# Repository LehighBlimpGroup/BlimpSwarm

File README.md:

# BLIMP SWARM
## [Click here for Documentation!](https://lehighblimpgroup.github.io/BlimpSwarm/)

BlimpSwarm is a framework to operate robots based on the ESP32 microcontroler.
### Please find [the indexed documentation here](https://github.com/LehighBlimpGroup/BlimpSwarm/blob/main/docs/index.md).

## FAQ

### Hardware

* Why does does only one servo or one motor not work, but the rest seem operational?
You likely have a loose/broken cable connection; If the cables are not broken (and need soldering or reinserting into the connecters), try just pushing the connectors together at every intersection. This can sometimes help the mechanical connecton to reoccur. 
If this does not solve your issue with one particular motor or servo, you might have a broken speed controller or a broken servo. Try using a test servo or test motor program to test these (or a servo tester if you have one). The motor itself can also break, and you can feel it by turining them by hand and observing the consistancy of the turning. The servo can be simalarly tested, but a servo is easier to break in this way. You can usually check if the servo is correcly powered by softly attempting to move them as they are powered and seeing if they want to move. One known issue is breaking servos due to insufficent current from the voltage booster. 

* Why does everything (motors and servos) turn on, but the robot doesnt seem to move up?
You likely have inverted motors or propellers. Make sure the propellers are correctly spinning in the correct direction and are pushing air down instead of up. If they are inverted, you need to switch any two wires in the connectors. You will need a sharp object to carefully lift the plastic blockers in the connecter to remove the wires and reinsert them in opposite positions (would recommend looking at a video).
Your robot might also be too heavy. 

* Why after I tried using all your troubleshooting tips, and I still cant solve the problem; I even used some methods you didnt mention and they failed!
There is a good chance the hardware on the PCB or the ESP32 failed. You may want to try replacing these to isolate the issue if possible to see if the issue still occurs. You may also be using an old version of the code, and may want to update the entire library to the github version. Sometimes the transeiver reduces in efficency from overuse, and the harware on the PCB can fail due to current spikes during operation. 

### Firmware

* The servos keep moving to weird positions when I start up, even though I set them to point up when the robot is in 'powered rest'. ( powered rest is the base setpoint of the servos when at rest, they should be pointing straight up).
This can be caused by the pitch feedback, try turning it off when trying. If you want pitch feedback and turining it off fixed this issue: set the pitch_offset parameter to 180 degrees from its current value. 

* Why does the flight work most of the time, but the turning while moving fowards seems very strange?
You likely have your servo1 connected to motor2 and vice versa. Check your hardware connections to make sure the front servo connection is on the same pair as the front motor connection. 

* Why does the pitch feedback fail force the servos to point straight up when it pitches, and go in the opposite direction?
Try setting inverting pitch_invert on the ground station from -1 to 1 or vice versa. 

* Why does my robot spin out of control when I start it up?
Try unplugging and replugging the blimp rapidly. Sometimes the capacitor causes the startup of the BNO to fail, and it will need a restart to correctly startup. 
Your yaw is likely inverted from the correct direction; try setting your kddyaw to negative or positive from its current direction. This is usally caused by the BNO being mounted upside down, but if that is required, you may need to edit the gains to accomidate for this. You can also double check by turining off yaw_en for yaw feedback, but your robot might unintentionally move in yaw due to the difference in servo angles when you first calibrate them. 

### Ground Station

* Why doesnt serial doesnt seem to be importing even though I did '$pip install pyserial'?: 
Your text editor is likely using a different version of python than the one you installed pyserial to: check to make sure these match or install pyserial to the installation of python used by your terminal/text editor.

* Why do I keep getting messages like "could not open port" when I run the ground station code?:
There are several reasons this could occur. 
#1 Make sure that your transiever code contains the correct 'BaseTranseiver.ino' code. 
#2 Make sure that your transiever arduino is connected to your computer, and check its port matches the one in 'user_parameters.py'.
#3 Make sure that the serial monitor of the transiever arduino is closed/not occupied by another process.

* Why isn't my blimp moving even though I turned the prorgram on?
#1 Make sure the robot is turned on.
    #a Make sure that you are sending an 'on' command in the python program (most use 'B' on the controller to start).
#2 Make sure the mac address in 'user_parameters.py' matches the mac address on the blimp.
#3 Make sure the robot code is correct: one of the bicopter.ino files ex: 'MultiRobotBicopter.ino'.
#4 Make sure the battery is charged (using a battery checker or at minimum, you hear the ESCs arm when you plug the battery in).
#5 Make sure the motors are calibrated, as the calibration might result in not seeing the motors move. 
#6 If the above fail, you can follow the following debugging procedures to isolate the issue:
#a Plug in the serial cable to the robot and observe the serial monitor:
    If the serial monitor is not printing statements that have to do with the start of a robot, or sensor measurements; you likely have the wrong firmware.
    If the serial montior is working as normal, continue.
#b Check the mac address of the robot and match it to the one in 'user_parameters.py'.
    If they are different, change and test again.
#c While observing the serial monitor, turn on the ground station code. You should see commands being recieved by the blimp on the serial monitor. (this will require two USB ports and cables) (You should not have the battery plugged into the blimp for this, unless you want to see the motors turn on while observing the serial monitor.)
    If you see nothing, you likely have some transmitter/reciever issues, but I would double check the firmware on the transeiver code, and the mac and ports are matching up on 'user_parameters.py'.
    If you see commands being recieved, you likely have a working robot, but if it still doesnt work, I would check to make sure the battery is OK and that the cables are connected correctly. Mismatches in the wiring could cause no movement even when commands are being received.

### Nicla Vision

* If you are not getting feedback from your niclavison on your arduino, you may try some of the following steps:
#1 double check that the nicla has the correct code, and it is properly downloaded on board as 'main.py'.
#2 connect the Serial monitor of your ESP32 on the blimp to the computer and make sure the nicla is powered and connected to the ESP32. Check to see if the serial monitor is getting values in the sensor measurements of the nicla (values 11-20) and that they are not crazy large values that occur when the nicla has not started up yet.
#3 double check that the nicla is properly powered, or directly connect it to your computer with a cable (will require 2 USB ports and cables)
    If you are sure that your nicla is seeing things and sending values, and you do not see anything on the ESP32 side even thought they are connected, you could have a broken Nicla vison or Nicla vision PCB. Check both by replacing them one at a time to see which is actually broken. The ESP32 PCB might also be broken but it is less likely.

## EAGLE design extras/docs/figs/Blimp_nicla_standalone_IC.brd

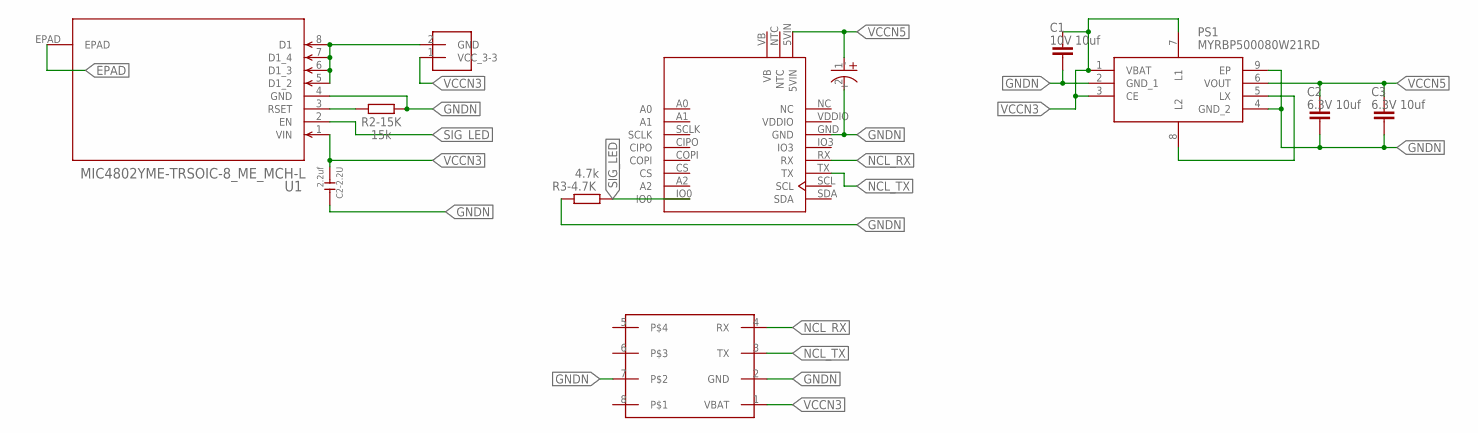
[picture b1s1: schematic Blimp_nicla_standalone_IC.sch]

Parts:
C1: 10V 10uf; CAPC1608X85
C2, C3: 6.3V 10uf; CAPC1608X85
C2-2.2U: 2.2uf; C0402
IR_LED1: UV_LIGHT
PS1: MYRBP500080W21RD
R2-15K: 15k; RESC1608X60
R3-4.7K: 4.7k; RESC1608X60
U1: MIC4802YME-TRSOIC-8_ME_MCH-L; SOIC-8_ME_MCH-L
U$6: NICLA_ESP_4PIN_CONNECTOR_MALE_ON_NICLA; ESP_NICLA_4X2PIN_CONNECTOR_MALE_ON_NICLA
U$9: CUSTOM_C; CAP
U$15: NICLAVISION; NICLA_FULL

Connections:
EPAD: U1.EPAD
GNDN: C1.2, C2.2, C2-2.2U.2, C3.2, PS1.2 (GND_1), PS1.4 (GND_2), PS1.9 (EP), R2-15K.2, R3-4.7K.2, U1.4 (GND), U$6.2 (GND), U$6.7, U$9.2 (-), U$15.GND
unnamed: IR_LED1.2 (GND), U1.5 (D1_2), U1.6 (D1_3), U1.7 (D1_4), U1.8 (D1)
unnamed: R2-15K.1, U1.3 (RSET)
unnamed: PS1.5 (LX), PS1.8 (L2)
NCL_RX: U$6.4 (RX), U$15.RX
NCL_TX: U$6.3 (TX), U$15.TX
SIG_LED: R3-4.7K.1, U1.2 (EN), U$15.IO0
VB: U$15.VB
VCCN3: C1.1, C2-2.2U.1, IR_LED1.1 (VCC_3-3), PS1.1 (VBAT), PS1.3 (CE), PS1.7 (L1), U1.1 (VIN), U$6.1 (VBAT)
VCCN5: C2.1, C3.1, PS1.6 (VOUT), U$9.1 (+), U$15.5VIN
VDDIO: U$15.VDDIO

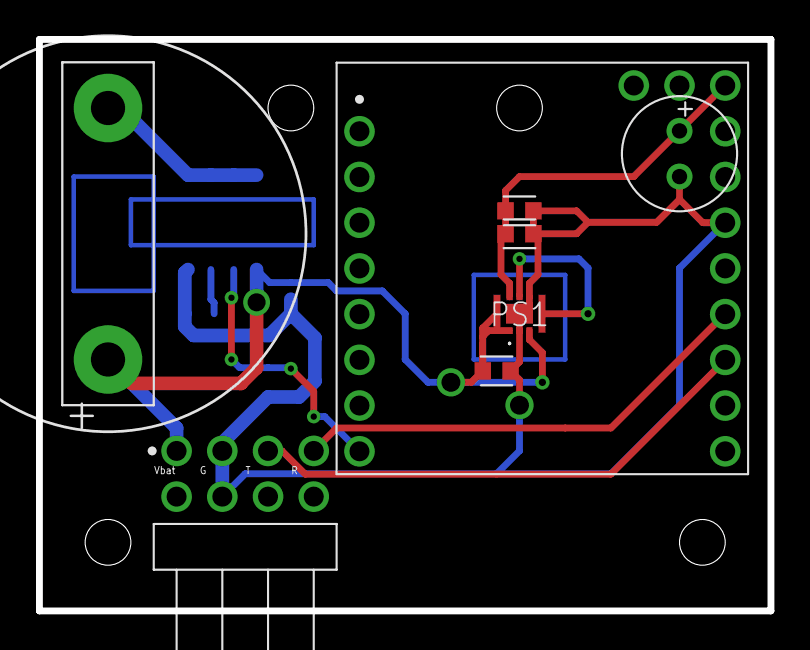
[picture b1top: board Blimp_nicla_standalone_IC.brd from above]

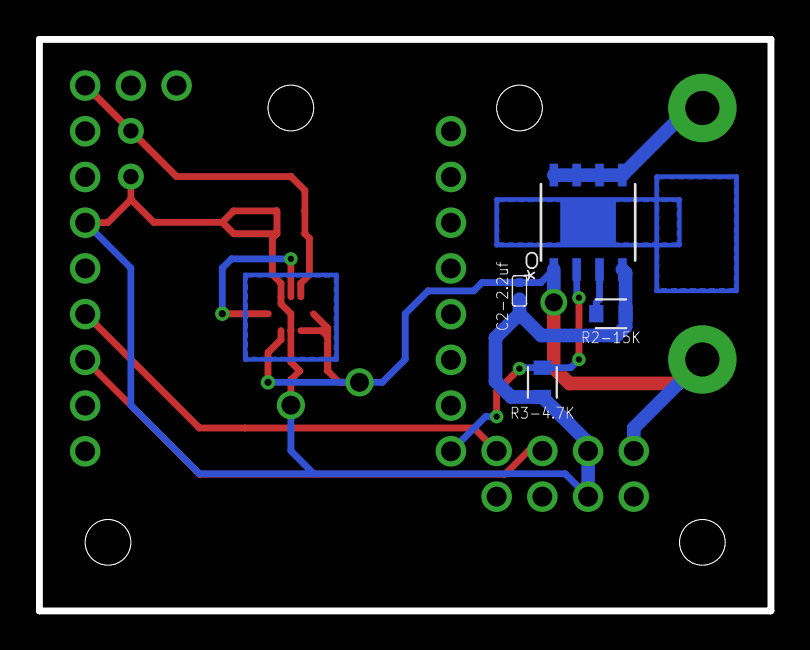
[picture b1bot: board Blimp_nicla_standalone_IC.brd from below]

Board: 2 copper layers, 40.6 x 31.8 mm, 12 parts (4 on the bottom side), 9 nets.

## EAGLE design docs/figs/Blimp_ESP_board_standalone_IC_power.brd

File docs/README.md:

# Simplest Jekyll
> A minimal Jekyll-based site on GH Pages, reduced to one page of content with a theme

<div align="center">

[_config.yml](_config.yml)
</div>

## Preview

<div align="center">
    
</div>

## About

This is a template and live demo project. It shows how little you need to setup to get a Jekyll site on GH Pages.

- [index.md](/index.md)
    - For the homepage - the only page in this case.
    - If you leave out this page, then `README.md` will be used as your homepage.
- [\_config.yml](/_config.yml)
    - Set the theme - that handles the layout and styling.
    - Enable Jekyll Sitemap plugin - enabling it in Gemfile is not enough. Note that other plugins will be enabled for you like optional frontmatter.
    - Other standard values like `baseurl`, `title` and `description` have been left out of the config. When building on GH Pages, these will be inferred for you by the GH Pages gem.
- [Gemfile](/Gemfile)
    - This is not actually used by GH Pages, but it allows you to install the Jekyll theme locally using Bundler. 
    - Use a single gem `github-pages` if you want to match all the gems on GH Pages (which can be heavy to install). 
    - Delete this file if you don't need to run your site locally.

If you want a more full-fledged example of a multi-page site with posts, gems, layouts, etc. then checkout my [jekyll-blog-demo](https://github.com/MichaelCurrin/jekyll-blog-demo) repo. That can be used as a template and demo site too.

## How to use this project

### Setup

1. Click _Use This Template_ to create a new repo in your own account. You can leave the name as `simplest-jekyll`.
2. Enable [GitHub Pages](https://pages.github.com/) in your repo's settings. Choose to serve from `master` branch and the `/` path option.
3. Check your repo's _environment_ tab to see when the deploy is done.
4. Click _View deployment_ to see the live site. e.g. https://michaelcurrin.github.io/simplest-jekyll/

Note that `/simplest-jekyll/index.html` is available immediately but it takes a few minutes until Github Pages makes `/simplest-jekyll/` available.

### Customize

- Update the `README.md` with your own details. This is not actually used in the deployed site but is visible locally and on Github.
- Themes
    - Edit the theme in [\_config.yml](/_config.yml) if you want another theme.
    - You can also use the Github Pages section of the repo Settings to preview visually. 
    - Note only themes supported by Github Pages are covered (about 10) but if you use the _remote_theme_ field in your config you can reference more themes.
    - For installing and running locally, you'll need to make sure your [Gemfile](/Gemfile) covers the theme used in the config.
- As with most Jekyll sites, the [index.md](/index.md) is used as the homepage. 
    - It has front matter at the top so any Liquid will be applied. 
    - Edit your `index.md` file with your own content as HTML or markdown. 
    - You can rename it to `index.html` if you only want plain HTML.
    - You can remove the front matter at the top to remove Liquid formatting and any theming.
- If you want to, add more pages at the root and break out any common HTMl such as header or head or navbar into `_includes` folder or `_layouts` folder (neither are covered in the scope of this project but are common for Jekyll projects).
- See the docs and tutorials on the [Jekyll](https:jekyllrb.com/) site for more info.
- Optionally run Jekyll locally:
    - Install Ruby and [Bundler](https://bundler.io).
    - Install project gems - Jekyll and the theme gem.
    - Run Jekyll dev server.
    - For fuller instructions see [docs](https://github.com/MichaelCurrin/jekyll-blog-demo/tree/master/docs) of Jekyll Blog Demo. You'll need to add a `Makefile` as well to match those commands.

## Related projects

-  - default blog generated with Jekyll CLI. Using a theme, content, style set up, gems, and a Makefile.
-  - using Jekyll 4, a theme, GitHub Actions, and GitHub Pages.
-  - minimal Jekyll site with a theme but no Gemfile.

## License

Released under [MIT](/LICENSE) by [@MichaelCurrin](https://github.com/MichaelCurrin).

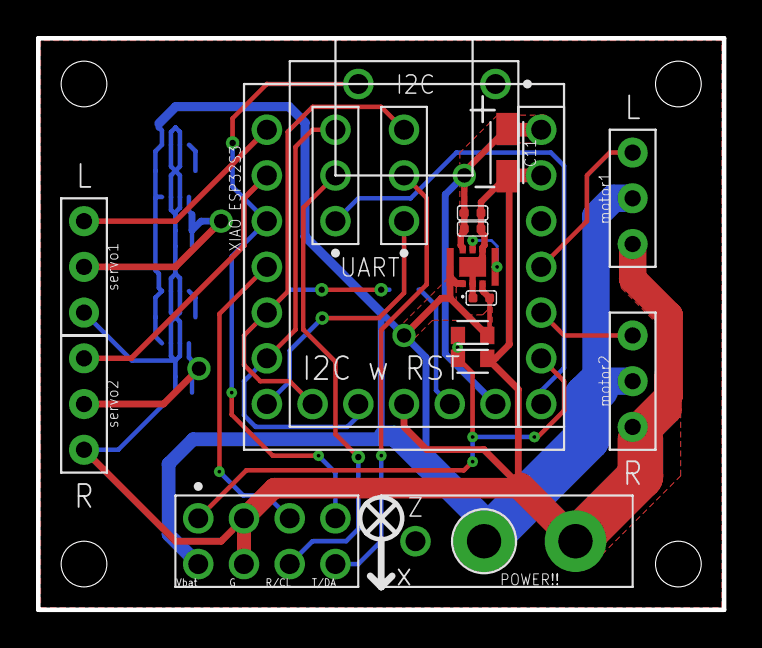
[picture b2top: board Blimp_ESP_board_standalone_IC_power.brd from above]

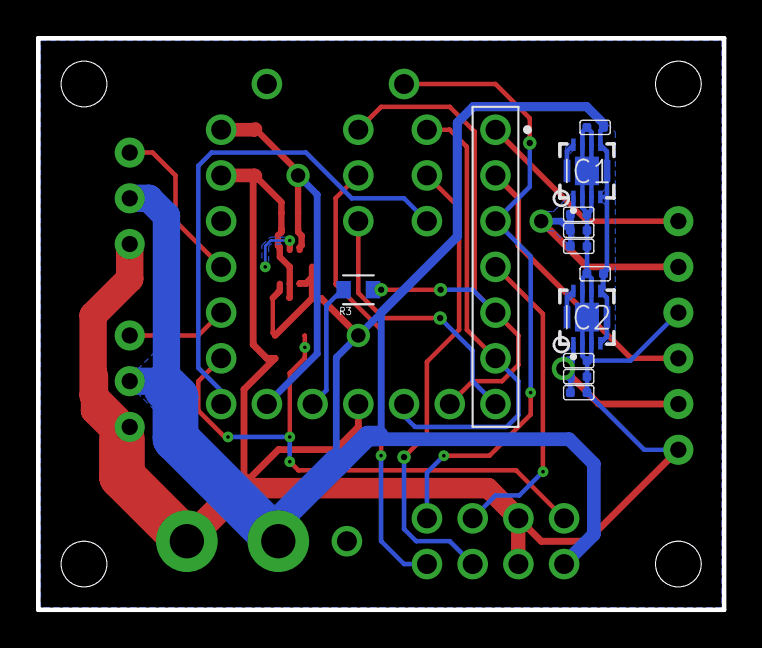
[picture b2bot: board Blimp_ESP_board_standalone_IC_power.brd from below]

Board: 2 copper layers, 38.1 x 31.8 mm, 28 parts (11 on the bottom side), 22 nets.

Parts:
ACT1, ACT2, ACT3, ACT4: ESC; ESC_CONECTOR_FOOT
C1, C2, C3, C4, C5, C6, C7, C8, C9, C10, C12: 10V 10uf; C0402
C11: CAPM3216X180
IC1, IC2: XCL104A501H2-G; DFN3030-10B
PS2: MYRBP500080W21RD
R1, R2: 470 Ohm; RESC1608X60
R3: 3.8K; RESC1608X60
U1: XIAOESP32S3
U$1: BATTERY_CONNECTOR; 3PIN_CONNECTOR_FEMALE
U$2: I2C_6PIN_WRST
U$4, U$5: 3X1SELECTOR
U$7: NICLA_ESP_4PIN_CONNECTOR_FEMALE_ON_ESP; ESP_NICLA_4X2PIN_CONNECTOR_FEMALE_ON_ESP

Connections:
3VOI2C: R3.1, U$2.9
D2: U1.3, U$2.16, U$7.4
D3: U1.4, U$7.3
D8: R1.2, R2.1, U1.9, U$7.1
ESP_RX/SCL: U$5.2, U$7.6
ESP_TX/SDA: U$4.2, U$7.5
GND: ACT1.1, ACT2.1, ACT3.1, ACT4.1, C1.2, C2.2, C3.2, C4.1, C5.2, C6.2, C7.1, C8.1, C9.1, C10.2, C11.2, C12.2, IC1.2, IC1.3, IC1.6, IC1.7, IC1.11, IC2.2, IC2.3, IC2.6, IC2.7, IC2.11, PS2.2, PS2.4, PS2.9, R2.2, U1.13, U$1.3, U$2.24, U$7.2, U$7.7
unnamed: IC1.8, IC1.9
unnamed: IC2.8, IC2.9
unnamed: PS2.5, PS2.8
RX: U1.8, U$5.1
SCL: U1.6, U$2.25, U$5.3
SDA: R3.2, U1.5, U$2.40, U$4.3
SIG1: ACT3.3, U1.1
SIG2: ACT2.3, U1.2
SIG3: ACT1.3, U1.10
SIG4: ACT4.3, U1.11
TX: U1.7, U$4.1
VBAT: ACT1.2, ACT4.2, C4.2, C7.2, C10.1, IC1.4, IC1.5, IC1.10, IC2.4, IC2.5, IC2.10, PS2.1, PS2.3, PS2.7, R1.1, U$1.2, U$7.8
VCC: C8.2, C9.2, C11.1, PS2.6, U1.14, U$2.8
VCCS1: ACT3.2, C2.1, C3.1, C12.1, IC1.1
VCCS2: ACT2.2, C1.1, C5.1, C6.1, IC2.1

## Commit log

2024-01-19 - File structure - Old files migration
2024-01-20 - Robot Factory is working - Compiled and tested on ESP
2024-01-23 - Test for ESPNow is created.
2024-01-27 - Receive data in ESP is working. - TestBaseCommESPNOW.ino is tested.
2024-01-28 - Send data in ESP is working. - TestBaseCommESPNOW.ino is tested.
2024-01-30 - Low level communication works for bytes only. Tested in ino.
2024-01-31 high level communication is working for cmd messages
2024-02-01 Parameter setup for drone
2024-02-02 Transmitter Changes
2024-02-02 Ground Station Params Test
2024-02-06 bugfix of float_min issue
2024-02-06 ground station interface
2024-02-07 Ready for test, RawBicopter unimplemented
2024-02-08 Joystick and communication are separated to independent files.
    - Joystick axes are mapped differently.
2024-02-08 RawBicopter.py can be called directly from the terminal
2024-02-08 control LED with left joystick
2024-02-08 Finished initial rawbicopter
2024-02-09 keyboard controls
2024-02-10 modularizing code for actuators
2024-02-10 battery sensor and communication is simpler.
2024-02-15 Barometer Setup
2024-02-15 class ready
2024-02-15 estimator adjustment
2024-02-15 Practice 2 is added
2024-02-15 parameter setting
2024-02-15 sqrt update
2024-02-15 preferences
2024-02-16 Calibration Working
2024-02-16 Fixing errors in folders
2024-02-21 - pwm to force conversion in BLMotor - Calibration in RawBicopter
2024-02-22 Bug fix in motors
    Motor documentation
2024-02-22 Ground Station Barometer Access
2024-02-22 base station setting
2024-02-22 GUI online
2024-02-29 test gihub page for documentation
2024-03-01 componenet list for the blimp
2024-03-01 Sensors in new framework working; test using TestSensors.ino
2024-03-01 adding photos
2024-03-02 Better visualization for initialization on sensors
2024-03-02 FullBicopter implementation
2024-03-06 adding assembly documentation
2024-03-07 Adjustments for differential controller and custombicopter
2024-03-08 Increased ease of use for sensors
2024-03-08 Ease of use change for interfacing with sensors
2024-03-09 SBlimp Capability
2024-03-11 BNO085 retry timer implementation
2024-03-14 Minor fixes in sensor rates
2024-03-14 Initial nicla tests
2024-03-14 Pitch inversion from ground station
2024-03-15 Nicla vision integration
2024-03-15 Behavior integration
2024-03-15 Consistency change
2024-03-18 Moving storage of ground height for consistancy.
2024-03-18 Increased wait time for refreshing BNO
2024-03-18 Added visual for nicla vision
2024-03-18 Prototype single-behavior for goal scoring
2024-03-19 270 servo bugfixes
2024-03-20 Barometer Bugfix
2024-03-21 CustomBicopter in ino
2024-03-21 Changes for classwork
2024-03-21 controls are more clear
2024-03-22 code for the class
2024-03-24 Documentation: firmware how to
2024-03-25 update documentation
2024-03-25 - user parameters are in a different file - Yaw Bicopter includes manual input
2024-03-25 - testing new controller
2024-03-25 270 servo bicopter
2024-03-25 State machine
2024-03-25 Startup change
2024-03-26 better gyro/accel from BNO
2024-03-26 cpython removal
2024-03-28 SkyKnot parameters
2024-03-28 yaw adjustments for tuning
2024-03-28 preferences added to sensors
2024-03-28 positive edge detection update
2024-03-28 minor adjustments
2024-03-28 pump files
2024-03-29 base station adjustments
2024-03-29 changes to base
2024-03-30 pump was added and LED actuator was removed
2024-04-07 BNO sensor startup bugfix
2024-04-08 BicopterFull manual example for class
2024-04-08 Goal Scoring Working version
2024-04-08 Hist pointer
2024-04-09 Reel and roll/pitch
2024-04-10 Setting midpoint on continuous servo
2024-04-11 Slight positive edge improvement for detection
2024-04-11 Nicla yaw enabled controller
2024-04-11 jiawei's test robot
2024-04-11 Class updates
2024-04-12 Updates for using height and nicla
2024-04-12 Update params from python
2024-04-12 Modifications for camera and LED
2024-04-12 bugfix for non-specific application
2024-04-14 nicla vision with balloon detection and capture - temporary parameters in use - positive-negative edge of detection implemented
2024-04-15 nicla vision with balloon detection and capture - first integration of balloon and goal capture - permanent config parameters in use - positive-negative edge of detection implemented - no balloon det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
2024-04-15 no auto send
2024-04-15 spinning included
2024-04-16 Controlling nicla vision external state
2024-04-16 spiral and levy walk integrated. log time in leavy is deactivated for now
2024-04-17 Resolved state transitions
2024-04-17 spiral and levy
2024-04-17 battery changes
2024-04-17 params
2024-04-18 Switching goal and balloon
2024-04-18 nicla vision with balloon detection and charge for 3 seconds once some criteria is satisfied - currently shifts state to levy walk after a charge
2024-04-18 nicla vision with balloon detection and charge for 3 seconds once some criteria is satisfied - fixed a bug wrt the positive detection edge
2024-04-18 yaw bugfix
2024-04-18 sub_state machine for transitions
2024-04-19 updated walk
2024-04-19 height and state change adjustments
2024-04-19 goal and ball height included in levy walk
2024-04-19 just spinning
2024-04-20 revert
2024-04-20 Multi-Robot System
2024-04-21 Tuining
2024-04-21 Goal changes
2024-04-23 Arming sequence before sensors
2024-04-23 Tensile and preferences
2024-04-23 The charge in balloon mode is constrained with centered balloon
2024-04-23 Levy for goal
2024-04-24 Improved spiral
2024-04-24 init changes
2024-04-24 minor macro change
2024-04-24 num captures issue
2024-04-24 Preferences bugfix
2024-04-24 constrain and macros
2024-04-24 Pump refinement
2024-04-25 multi robot macros
2024-04-25 Fix param update
2024-04-26 Different detection
2024-05-02 Goal start for terms
2024-05-02 FAQ start
2024-06-11 update GUI feedback
2024-06-12 add direct mapping code
2024-06-17 Add code for CHOICES program
2024-06-19 ID address
2024-06-21 add documentation for actuation files
2024-06-24 Update to files
2024-06-28 Add initial documentation of state machine
2024-07-01 Finish documentation for state machine
2024-07-02 Add documentation for comm
2024-07-24 Fix issue with manual state transition and change charge behavior
2024-08-08 kalman initial commit
2024-08-09 add doxyfile, finish src/ documentation
2024-08-14 Add MAC addresses for 12 robots. Adjustment to preferences.
2024-08-15 Fix issue with PDTerms
2024-08-15 Change Robot1 and Robot2 for Prelusion
2024-08-27 update levy walk's height exploration
2024-09-03 Latest Kalman Filter updates
2024-09-03 Latest updates on the Kalman Filter-based localization module
2024-10-04 still need to figure out protocol
2024-10-07 Add Differential Robot Type
2024-10-09 Update macs
2024-10-22 testing communication between 2 boards
2024-10-23 UI working
2024-10-23 optimised differential control on yaw and hover behavior
2024-10-25 better differential tune
2024-11-01 testing sensors work
2024-11-02 Wall detection and avoidance using ultrasonic sensor
    1. Ultrasonic sensor included in sensor suite
    2. Wall detection and avoidance incorporated in Levywalk
2024-11-02 360 diff
2024-11-03 updates to Blimpswarm/swarmbase
2024-11-05 fix differential 360
2024-11-05 Fix preferences issue
2024-11-06 Minor changes to main-ultrasonic branch after testing them in differential-ultrasonic Works fine in the absence of vison module
2024-11-06 fix issues with keyboard input and gui
2024-11-06 Fix bug with nicla pursuit
2024-11-06 preferences are able to be sent mid flight
2024-11-06 Fix parameter for specific robot
2024-11-08 fix broadcast parameter send
2024-11-08 levy walk code, preferences to lower case
2024-11-08 Tensile
2024-11-10 modifications to levywalk and parameters
2024-11-10 Add spiral to levy walk
2024-11-10 give arguments to functions
2024-11-13 tensile
    11
2024-11-14 add tensile robot control
2024-11-14 update state machine and add levyspiral params
2024-11-18 fix to paramUpdate
2024-11-18 no yaw on goal charge, minimum height enforced during moveToGoal
2024-11-20 add new levy spiral algorithm
2024-11-21 fix levywalk and initial charge forward
2024-11-21 add color switch
2024-11-22 change levy spiral
2024-11-22 final levy walk
2024-11-24 sensor data can receive
2024-11-25 working yayyy
2024-12-13 Add absolute yaw sensor and update sensor test code
2025-03-05 update changes for reel
2025-03-17 Levy spiral using yaw instead of time
2025-04-18 add broadcast commands and preference comments
2025-04-18 remove initial forward motion
2025-04-18 fix ultrasonic
2025-04-19 fix tensile
2025-04-19 fix levy walk and preferences
2025-04-20 fix levy walk and parameters
2025-04-21 change to wall detection and preferences for reelSpeed
2025-04-23 changes to levy walk
2025-09-17 remove unnecessary artifacts
2025-11-02 fix comm incompatibility
2025-11-12 init
2025-11-12 Added mocap data collection. TODO: Compare with IMU data
2025-11-14 adding inputs
2025-11-21 data collection
2025-11-21 aSaves data as dict of numpy arrays, and a basic visualization tool for pitch angles
2025-11-24 data filter
2025-12-01 robot rotation monitoring
2025-12-01 data
2025-12-02 no mocap control
2025-12-03 copy doc folder for the githubpage from agile blimp to main
2025-12-03 get rid of duplicate
2025-12-03 removed print
2025-12-03 mac add
2025-12-03 copying changes
2025-12-03 onboard sensor info is correct, transeiver or python breaks it
2025-12-04 fixed bad Serial.print() in base transeiver, that prints the text in serial, thus corrupting the senor data
2025-12-04 Changes made: 1. incresed size of data_array in BNO 2. Validated that new acc data is received on robot board(esp). rcv.data is now incresed to include acceleration and rates 3. [ISSUE] Data is not b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
2025-12-04 Changes : 1. I removed the limit on how fast BaseCommunicator can send data. So now, it sends data whenever it is called. L77 breaks for some reason, the timer is reset maybe?
    2. Forces it to enter in manual in diff controller
    3. Serial.py now unpacks 52 bytes
2025-12-05 Dada viz files, going in circle data. Use in_circle_data_6.pkl Data format is (timestamp, sensor_array, mocap_array) sensor_array: [height, pitch_body, -roll_body, yaw_body, pitch_rate, -roll_rate, y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
2025-12-05 Saved data in circle data.
2025-12-09 Just a lot of collected data for model training.
2025-12-09 additional data
2025-12-09 more aggressive data
2025-12-09 acc puahing data vin 2
2026-03-19 fix compilation error for DiffController.ino

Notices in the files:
docs/README.md:
License: MIT
parts and their libraries:
COPYRIGHT: Copyright (C) 2024 Ultra Librarian. All rights reserved.
